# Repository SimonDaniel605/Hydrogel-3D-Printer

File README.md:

# Hydrogel-3D-Printer

This project aims at the development of a custom hydrogel 3D printer for tissue engineering and research applications for Stellenbosch University. This is a 4th year project for SU's BEng Mechatronics program.

This repository contains the PCB design files, firmware, and supporting documentation for the Hydrogel 3D Printer project.

Name: Simon Craig DANIEL

Student Number: 25848887

Supervisor: Mr. Wayne Swart

Company: Stellenbosch University

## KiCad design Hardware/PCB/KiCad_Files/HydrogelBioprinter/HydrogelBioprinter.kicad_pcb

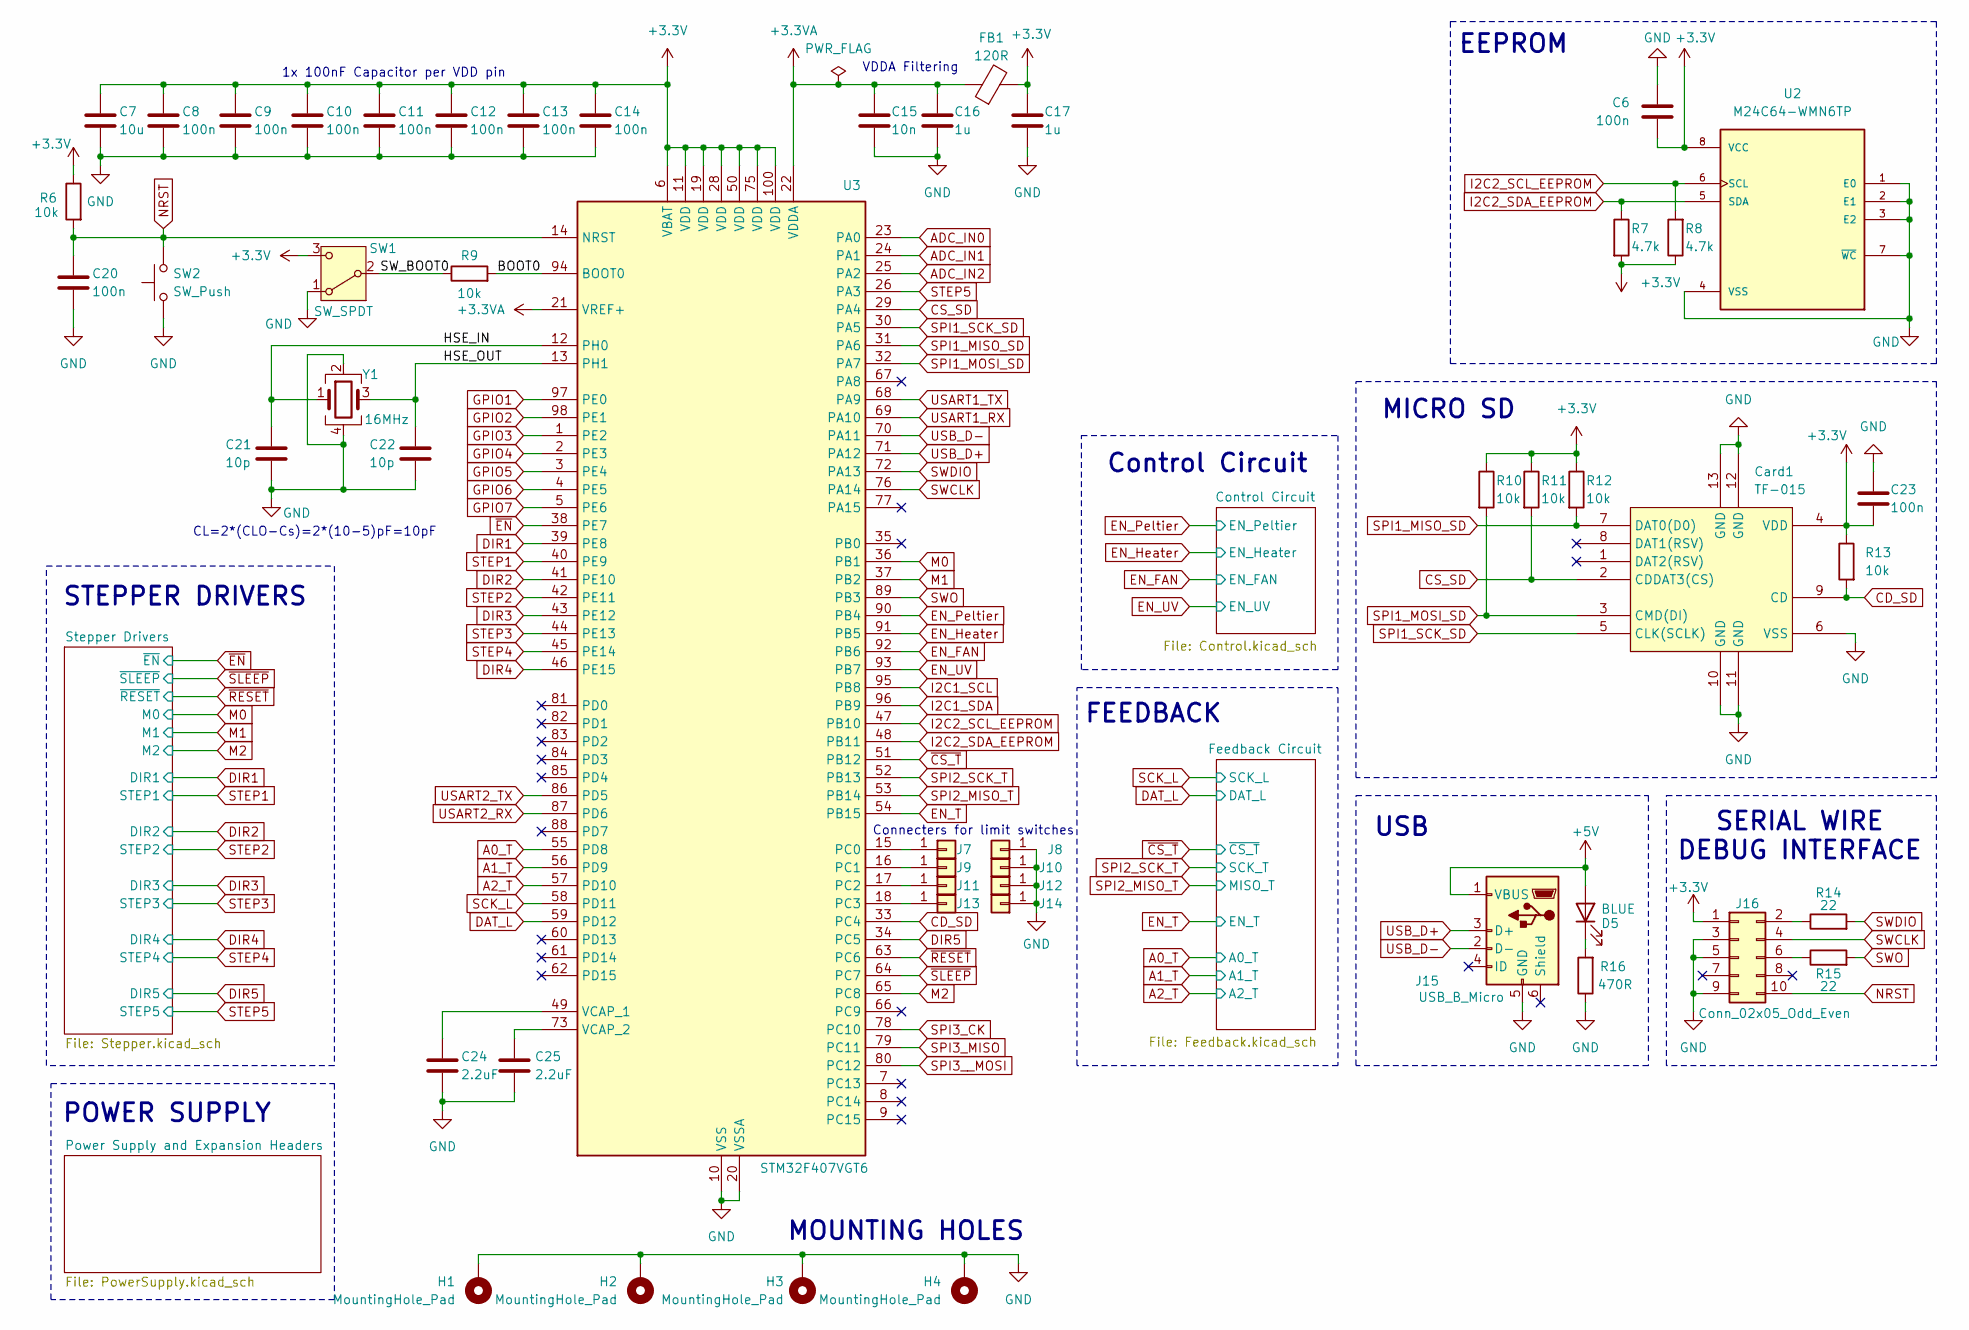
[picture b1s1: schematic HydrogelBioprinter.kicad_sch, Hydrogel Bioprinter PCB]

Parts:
C6, C8, C9, C10, C11, C12, C13, C14, C20, C23: 100n; C_0603_1608Metric
C7: 10u; C_0805_2012Metric
C15: 10n; C_0603_1608Metric
C16, C17: 1u; C_0805_2012Metric
C21, C22: 10p; C_0402_1005Metric
C24, C25: 2.2uF; C_0805_2012Metric
Card1: TF-015; TF-SMD_TF-015; LCSC Part C113206
D5: BLUE; LED_0805_2012Metric
FB1: 120R; L_0805_2012Metric
H1, H2, H3, H4: MountingHole_Pad; MountingHole_4.3mm_M4_Pad
J7, J8, J9, J10, J11, J12, J13, J14: Conn; SolderWire-0.75sqmm_1x01_D1.25mm_OD3.5mm
J15: USB_B_Micro; USB_Micro-B_Molex-105017-0001
J16: Conn_02x05_Odd_Even; PinHeader_2x05_P2.54mm_Vertical_SMD
R6, R9, R10, R11, R12, R13: 10k; R_0805_2012Metric
R7, R8: 4.7k; R_0805_2012Metric
R14, R15: 22; R_0603_1608Metric
R16: 470R; R_Axial_DIN0207_L6.3mm_D2.5mm_P10.16mm_Horizontal
SW1: SW_SPDT; SW_SPDT_PCM12
SW2: SW_Push; SW_PUSH_6mm
U2: M24C64-WMN6TP; SOIC127P600X175-8N; PARTREV 38; DigiKey_Part_Number 497-8650-2-ND
U3: STM32F407VGT6; LQFP-100_14x14mm_P0.5mm
Y1: 16MHz; Crystal_SMD_3225-4Pin_3.2x2.5mm

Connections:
+3.3V: C6.2, C7.1, C8.1, C9.1, C10.1, C11.1, C12.1, C13.1, C14.1, C17.1, C23.2, Card1.4 (VDD), FB1.2, J16.1, R6.1, R7.2, R8.1, R10.1, R11.1, R12.1, R13.1, SW1.3 (C), U2.8 (VCC), U3.6 (VBAT), U3.11 (VDD), U3.19 (VDD), U3.28 (VDD), U3.50 (VDD), U3.75 (VDD), U3.100 (VDD); also elsewhere on the board
+3.3VA: C15.1, C16.1, FB1.1, U3.21 (VREF+), U3.22 (VDDA)
+5V: D5.2 (A), J15.1 (VBUS)
/BOOT0: R9.2, U3.94 (BOOT0)
/HSE_IN: C21.1, U3.12 (PH0), Y1.1
/HSE_OUT: C22.1, U3.13 (PH1), Y1.3
/SW_BOOT0: R9.1, SW1.2 (B)
A0_T: U3.55 (PD8); also elsewhere on the board
A1_T: U3.56 (PD9); also elsewhere on the board
A2_T: U3.57 (PD10); also elsewhere on the board
ADC_IN0: U3.23 (PA0); also elsewhere on the board
ADC_IN1: U3.24 (PA1); also elsewhere on the board
ADC_IN2: U3.25 (PA2); also elsewhere on the board
CD_SD: Card1.9 (CD), R13.2, U3.33 (PC4)
CS_SD: Card1.2 (CDDAT3(CS)), R11.2, U3.29 (PA4)
DAT_L: U3.59 (PD12); also elsewhere on the board
DIR1: U3.39 (PE8); also elsewhere on the board
DIR2: U3.41 (PE10); also elsewhere on the board
DIR3: U3.43 (PE12); also elsewhere on the board
DIR4: U3.46 (PE15); also elsewhere on the board
DIR5: U3.34 (PC5); also elsewhere on the board
EN_FAN: U3.92 (PB6); also elsewhere on the board
EN_Heater: U3.91 (PB5); also elsewhere on the board
EN_Peltier: U3.90 (PB4); also elsewhere on the board
EN_T: U3.54 (PB15); also elsewhere on the board
EN_UV: U3.93 (PB7); also elsewhere on the board
GND: C6.1, C7.2, C8.2, C9.2, C10.2, C11.2, C12.2, C13.2, C14.2, C15.2, C16.2, C17.2, C20.2, C21.2, C22.2, C23.1, C24.2, C25.2, Card1.6 (VSS), Card1.10 (GND), Card1.11 (GND), Card1.12 (GND), Card1.13 (GND), H1.1, H2.1, H3.1, H4.1, J8.1, J10.1, J12.1, J14.1, J15.5 (GND), J16.3, J16.5, J16.9, R16.1, SW1.1 (A), SW2.1, U2.1 (E0), U2.2 (E1), U2.3 (E2), U2.4 (VSS), U2.7 (~WC), U3.10 (VSS), U3.20 (VSSA), U3.27 (VSS), U3.74 (VSS), U3.99 (VSS), Y1.2, Y1.4; also elsewhere on the board
GPIO1: U3.97 (PE0); also elsewhere on the board
GPIO2: U3.98 (PE1); also elsewhere on the board
GPIO3: U3.1 (PE2); also elsewhere on the board
GPIO4: U3.2 (PE3); also elsewhere on the board
GPIO5: U3.3 (PE4); also elsewhere on the board
GPIO6: U3.4 (PE5); also elsewhere on the board
GPIO7: U3.5 (PE6); also elsewhere on the board
I2C1_SCL: U3.95 (PB8); also elsewhere on the board
I2C1_SDA: U3.96 (PB9); also elsewhere on the board
I2C2_SCL_EEPROM: R8.2, U2.6 (SCL), U3.47 (PB10)
I2C2_SDA_EEPROM: R7.1, U2.5 (SDA), U3.48 (PB11)
M0: U3.36 (PB1); also elsewhere on the board
M1: U3.37 (PB2); also elsewhere on the board
M2: U3.65 (PC8); also elsewhere on the board
NRST: C20.1, J16.10, R6.2, SW2.2, U3.14 (NRST)
unnamed: D5.1 (K), R16.2
unnamed: J7.1, U3.15 (PC0)
unnamed: J9.1, U3.16 (PC1)
unnamed: J11.1, U3.17 (PC2)
unnamed: J13.1, U3.18 (PC3)
unnamed: J16.2, R14.1
unnamed: J16.6, R15.1
unnamed: C24.1, U3.49 (VCAP_1)
unnamed: C25.1, U3.73 (VCAP_2)
SCK_L: U3.58 (PD11); also elsewhere on the board
SPI1_MISO_SD: Card1.7 (DAT0(D0)), R12.2, U3.31 (PA6)
SPI1_MOSI_SD: Card1.3 (CMD(DI)), R10.2, U3.32 (PA7)
SPI1_SCK_SD: Card1.5 (CLK(SCLK)), U3.30 (PA5)
SPI2_MISO_T: U3.53 (PB14); also elsewhere on the board
SPI2_SCK_T: U3.52 (PB13); also elsewhere on the board
SPI3_CK: U3.78 (PC10); also elsewhere on the board
SPI3_MISO: U3.79 (PC11); also elsewhere on the board
SPI3__MOSI: U3.80 (PC12); also elsewhere on the board
STEP1: U3.40 (PE9); also elsewhere on the board
STEP2: U3.42 (PE11); also elsewhere on the board
STEP3: U3.44 (PE13); also elsewhere on the board
STEP4: U3.45 (PE14); also elsewhere on the board
STEP5: U3.26 (PA3); also elsewhere on the board
SWCLK: J16.4, U3.76 (PA14)
SWDIO: R14.2, U3.72 (PA13)
SWO: R15.2, U3.89 (PB3)
USART1_RX: U3.69 (PA10); also elsewhere on the board
USART1_TX: U3.68 (PA9); also elsewhere on the board
USART2_RX: U3.87 (PD6); also elsewhere on the board
USART2_TX: U3.86 (PD5); also elsewhere on the board
USB_D+: J15.3 (D+), U3.71 (PA12)
USB_D-: J15.2 (D-), U3.70 (PA11)
~CS_T: U3.51 (PB12); also elsewhere on the board
~EN: U3.38 (PE7); also elsewhere on the board
~RESET: U3.63 (PC6); also elsewhere on the board
~SLEEP: U3.64 (PC7); also elsewhere on the board

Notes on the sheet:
VDDA Filtering
FEEDBACK
SERIAL WIRE DEBUG INTERFACE
Connecters for limit switches
USB
MOUNTING HOLES
MICRO SD
STEPPER DRIVERS
CL=2*(CLO-Cs)=2*(10-5)pF=10pF
Control Circuit
EEPROM
POWER SUPPLY
1x 100nF Capacitor per VDD pin

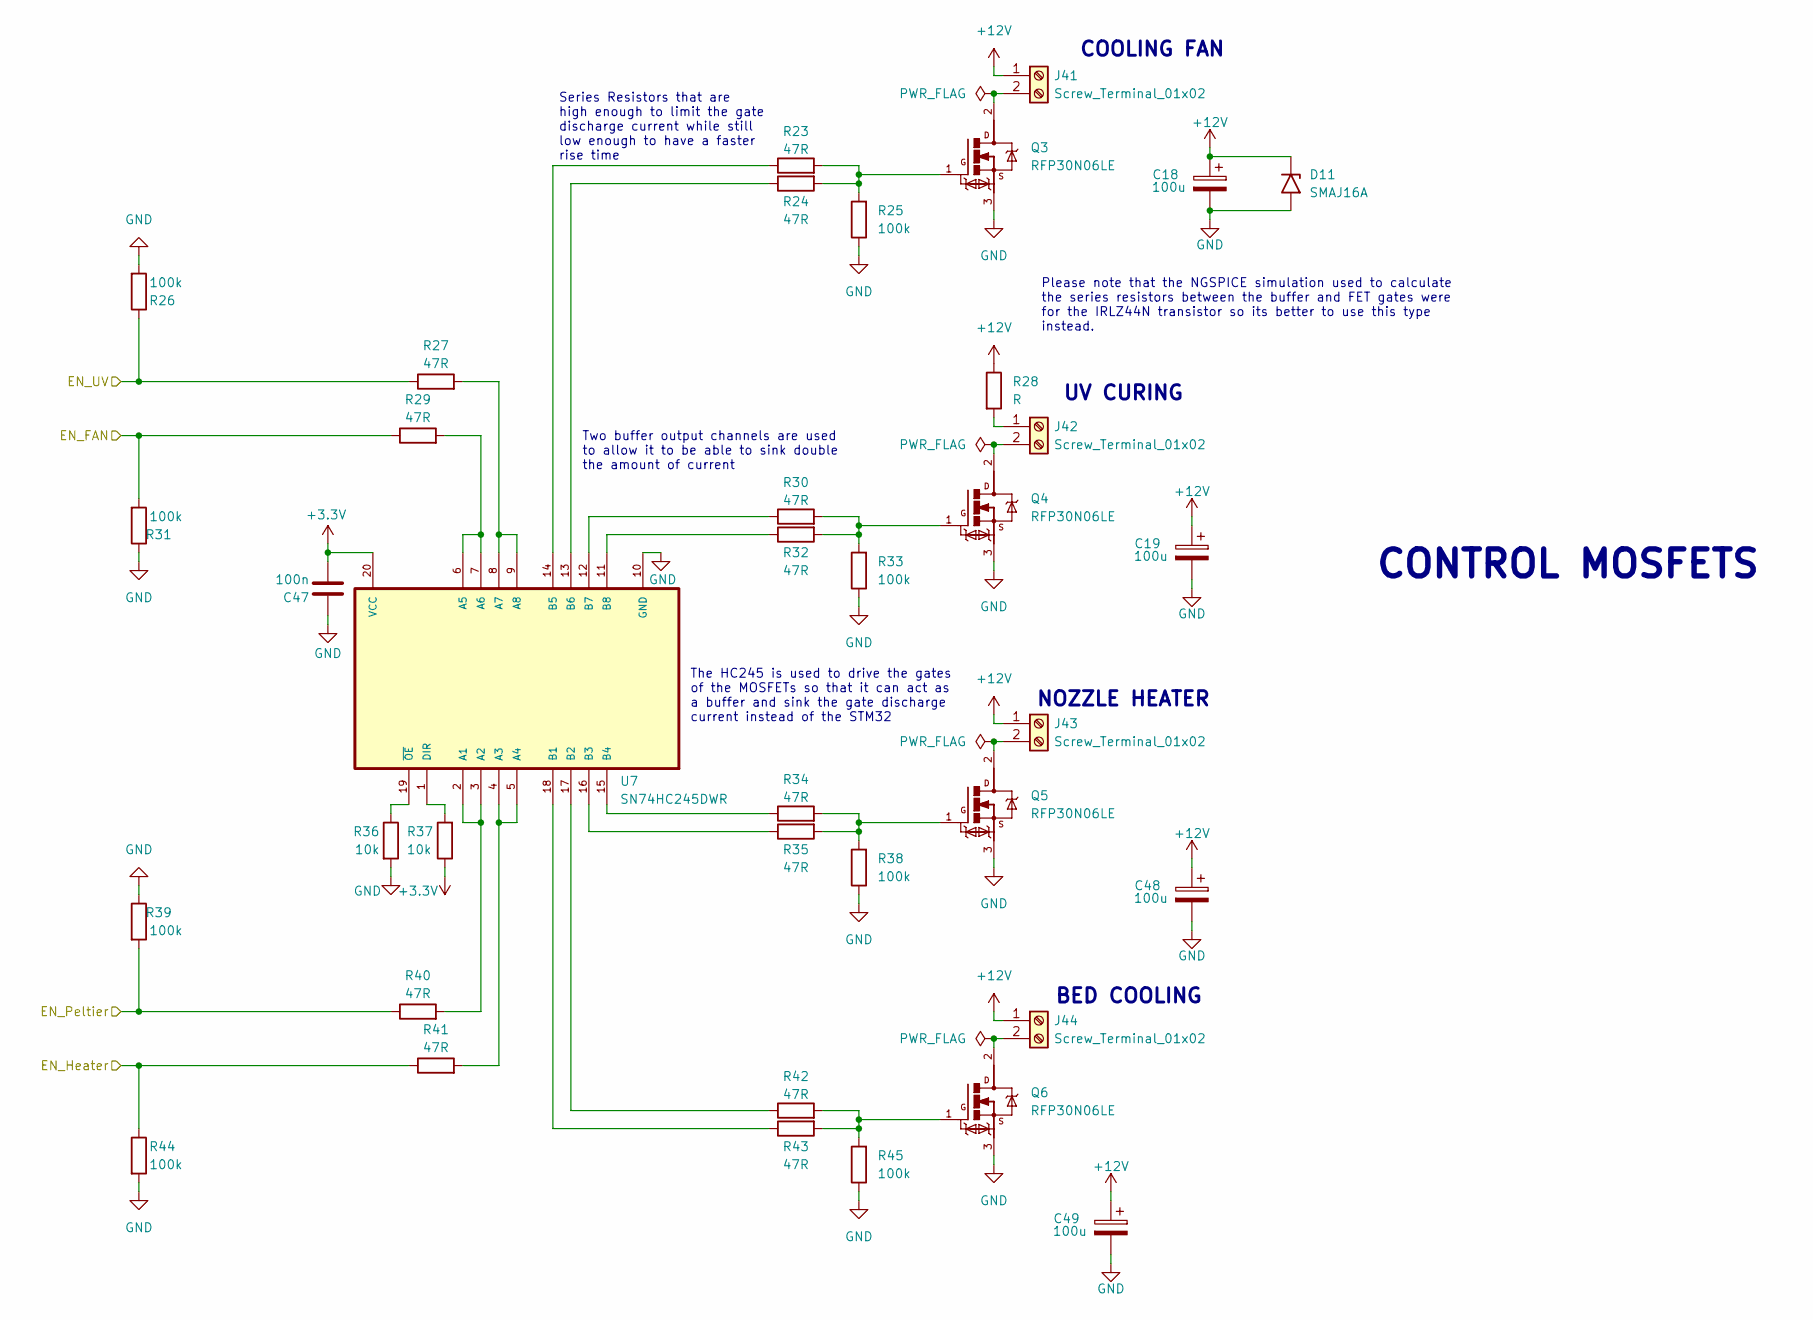
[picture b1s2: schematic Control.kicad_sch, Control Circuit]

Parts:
C18, C19, C48, C49: 100u; CP_Elec_6.3x7.7
C47: 100n; C_0603_1608Metric
D11: SMAJ16A; D_SMA
J41, J42, J43, J44: Screw_Terminal_01x02; TerminalBlock_Phoenix_MKDS-1,5-2-5.08_1x02_P5.08mm_Horizont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
Q3, Q4, Q5, Q6: RFP30N06LE; TRANS_RFP30N06LE
R23, R24, R27, R29, R30, R32, R34, R35, R40, R41, R42, R43: 47R; R_0805_2012Metric
R25, R26, R31, R33, R38, R39, R44, R45: 100k; R_0805_2012Metric
R28: R; R_Axial_DIN0207_L6.3mm_D2.5mm_P10.16mm_Horizontal
R36, R37: 10k; R_0805_2012Metric
U7: SN74HC245DWR; SOIC127P1030X265-20N

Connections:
+3.3V: C47.1, R37.1, U7.20 (VCC); also elsewhere on the board
+12V: C18.1, C19.1, C48.1, C49.1, D11.1 (A1), J41.1, J43.1, J44.1, R28.1; also elsewhere on the board
EN_FAN: R29.1, R31.2; also elsewhere on the board
EN_Heater: R41.1, R44.1; also elsewhere on the board
EN_Peltier: R39.2, R40.1; also elsewhere on the board
EN_UV: R26.1, R27.1; also elsewhere on the board
GND: C18.2, C19.2, C47.2, C48.2, C49.2, D11.2 (A2), Q3.3, Q4.3, Q5.3, Q6.3, R25.1, R26.2, R31.1, R33.1, R36.2, R38.1, R39.1, R44.2, R45.1, U7.10 (GND); also elsewhere on the board
unnamed: J41.2, Q3.2
unnamed: J42.1, R28.2
unnamed: J42.2, Q4.2
unnamed: J43.2, Q5.2
unnamed: J44.2, Q6.2
unnamed: Q3.1, R23.2, R24.2, R25.2
unnamed: Q4.1, R30.2, R32.2, R33.2
unnamed: Q5.1, R34.2, R35.2, R38.2
unnamed: Q6.1, R42.2, R43.2, R45.2
unnamed: R40.2, U7.2 (A1), U7.3 (A2)
unnamed: R41.2, U7.4 (A3), U7.5 (A4)
unnamed: R29.2, U7.6 (A5), U7.7 (A6)
unnamed: R27.2, U7.8 (A7), U7.9 (A8)
unnamed: R43.1, U7.18 (B1)
unnamed: R42.1, U7.17 (B2)
unnamed: R35.1, U7.16 (B3)
unnamed: R34.1, U7.15 (B4)
unnamed: R23.1, U7.14 (B5)
unnamed: R24.1, U7.13 (B6)
unnamed: R30.1, U7.12 (B7)
unnamed: R32.1, U7.11 (B8)
unnamed: R37.2, U7.1 (DIR)
unnamed: R36.1, U7.19 (~OE)

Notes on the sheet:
UV CURING
NOZZLE HEATER
COOLING FAN
Two buffer output channels are used to allow it to be able to sink double the amount of current
The HC245 is used to drive the gates of the MOSFETs so that it can act as a buffer and sink the gate discharge current instead of the STM32
Please note that the NGSPICE simulation used to calculate the series resistors between the buffer and FET gates were for the IRLZ44N transistor so its better to use this type instead.
CONTROL MOSFETS
Series Resistors that are high enough to limit the gate discharge current while still low enough to have a faster rise time
BED COOLING

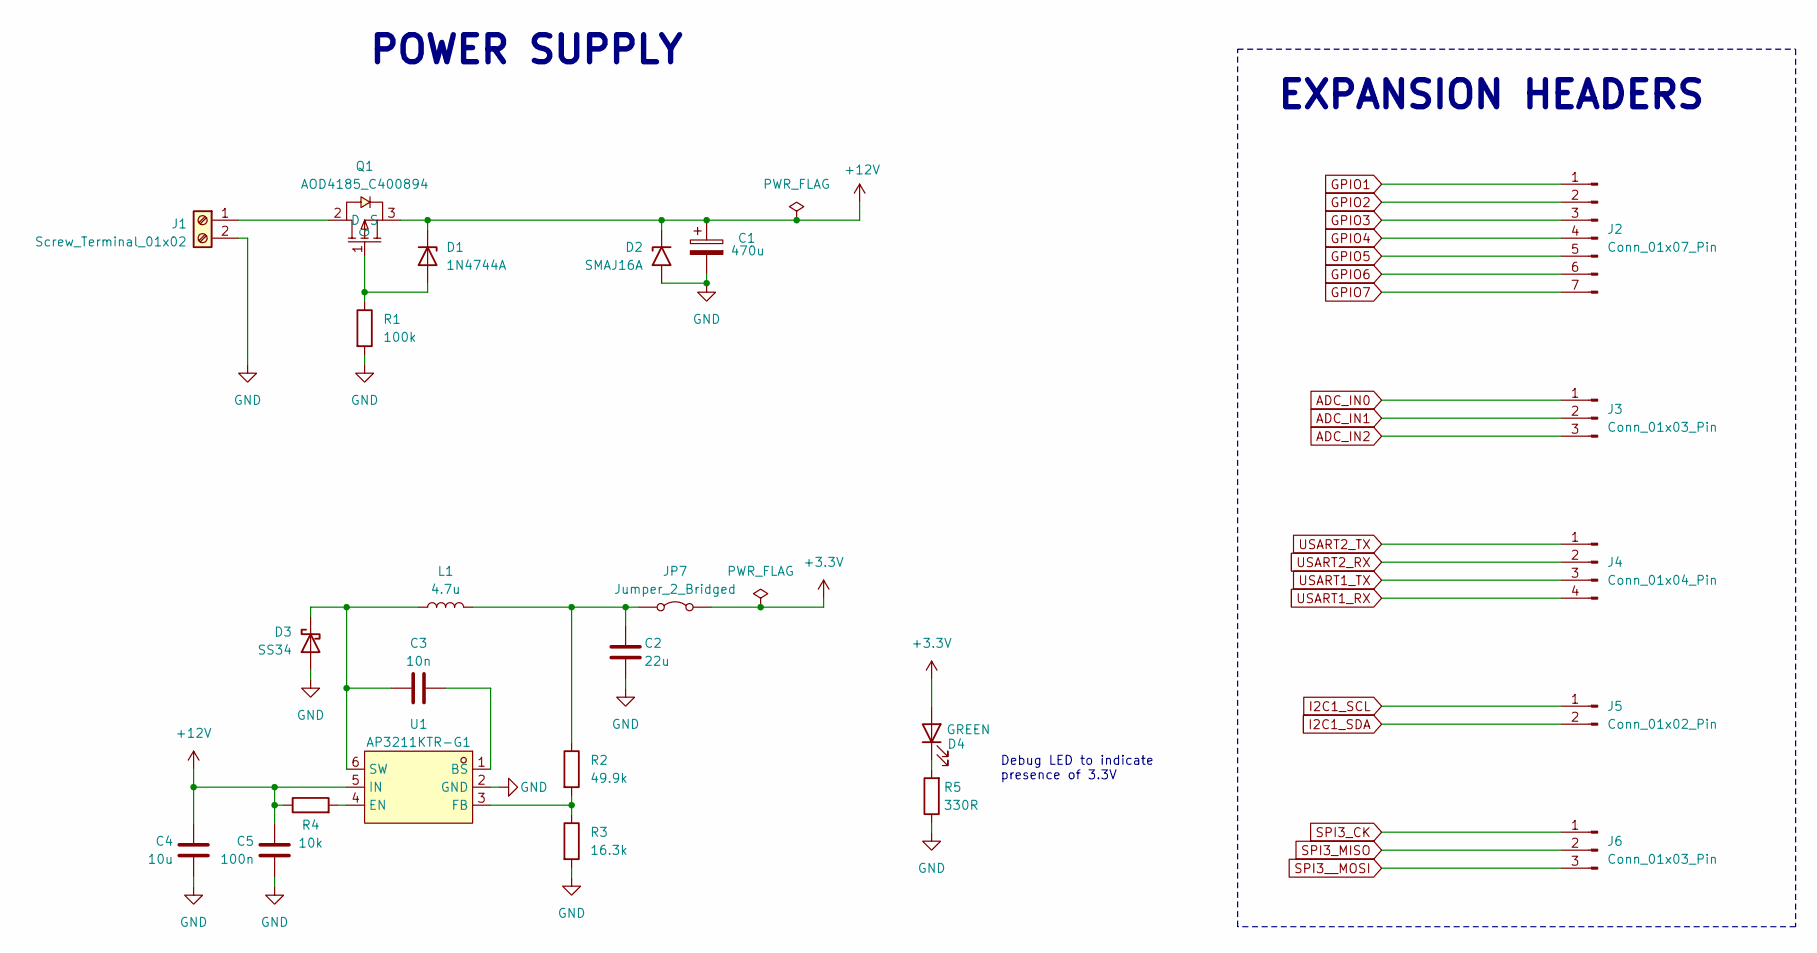
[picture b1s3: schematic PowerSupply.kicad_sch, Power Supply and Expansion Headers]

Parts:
C1: 470u; CP_Radial_D10.0mm_P5.00mm
C2: 22u; C_0805_2012Metric
C3: 10n; C_0603_1608Metric
C4: 10u; C_0805_2012Metric
C5: 100n; C_0603_1608Metric
D1: 1N4744A; D_DO-41_SOD81_P10.16mm_Horizontal
D2: SMAJ16A; D_SMA
D3: SS34; D_SMA
D4: GREEN; LED_0805_2012Metric
J1: Screw_Terminal_01x02; TerminalBlock_Phoenix_MKDS-1,5-2-5.08_1x02_P5.08mm_Horizont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
J2: Conn_01x07_Pin; PinHeader_1x07_P2.54mm_Vertical
J3, J6: Conn_01x03_Pin; PinHeader_1x03_P2.54mm_Vertical
J4: Conn_01x04_Pin; PinHeader_1x04_P2.54mm_Vertical
J5: Conn_01x02_Pin; PinHeader_1x02_P2.54mm_Vertical
JP7: Jumper_2_Bridged; TestPoint_2Pads_Pitch2.54mm_Drill0.8mm
L1: 4.7u; L_7.3x7.3_H4.5
Q1: AOD4185_C400894; TO-252-3_L6.6-W6.1-P4.57-LS9.9-BR-CW; LCSC Part C400894
R1: 100k; R_0805_2012Metric
R2: 49.9k; R_Axial_DIN0207_L6.3mm_D2.5mm_P10.16mm_Horizontal
R3: 16.3k; R_Axial_DIN0207_L6.3mm_D2.5mm_P10.16mm_Horizontal
R4: 10k; R_0805_2012Metric
R5: 330R; R_Axial_DIN0207_L6.3mm_D2.5mm_P10.16mm_Horizontal
U1: AP3211KTR-G1; LCSC Part C154863

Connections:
+3.3V: D4.2 (A), JP7.1 (A); also elsewhere on the board
+12V: C1.1, C4.2, C5.2, D1.1 (K), D2.1 (A1), Q1.3 (S), R4.1, U1.5 (IN); also elsewhere on the board
ADC_IN0: J3.1; also elsewhere on the board
ADC_IN1: J3.2; also elsewhere on the board
ADC_IN2: J3.3; also elsewhere on the board
GND: C1.2, C2.2, C4.1, C5.1, D2.2 (A2), D3.2 (A), J1.2, R1.2, R3.2, R5.1, U1.2 (GND); also elsewhere on the board
GPIO1: J2.1; also elsewhere on the board
GPIO2: J2.2; also elsewhere on the board
GPIO3: J2.3; also elsewhere on the board
GPIO4: J2.4; also elsewhere on the board
GPIO5: J2.5; also elsewhere on the board
GPIO6: J2.6; also elsewhere on the board
GPIO7: J2.7; also elsewhere on the board
I2C1_SCL: J5.1; also elsewhere on the board
I2C1_SDA: J5.2; also elsewhere on the board
unnamed: D1.2 (A), Q1.1 (G), R1.1
unnamed: C3.1, D3.1 (K), L1.1, U1.6 (SW)
unnamed: D4.1 (K), R5.2
unnamed: J1.1, Q1.2 (D)
unnamed: C2.1, JP7.2 (B), L1.2, R2.1
unnamed: C3.2, U1.1 (BS)
unnamed: R4.2, U1.4 (EN)
unnamed: R2.2, R3.1, U1.3 (FB)
SPI3_CK: J6.1; also elsewhere on the board
SPI3_MISO: J6.2; also elsewhere on the board
SPI3__MOSI: J6.3; also elsewhere on the board
USART1_RX: J4.4; also elsewhere on the board
USART1_TX: J4.3; also elsewhere on the board
USART2_RX: J4.2; also elsewhere on the board
USART2_TX: J4.1; also elsewhere on the board

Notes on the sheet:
EXPANSION HEADERS
POWER SUPPLY
Debug LED to indicate presence of 3.3V

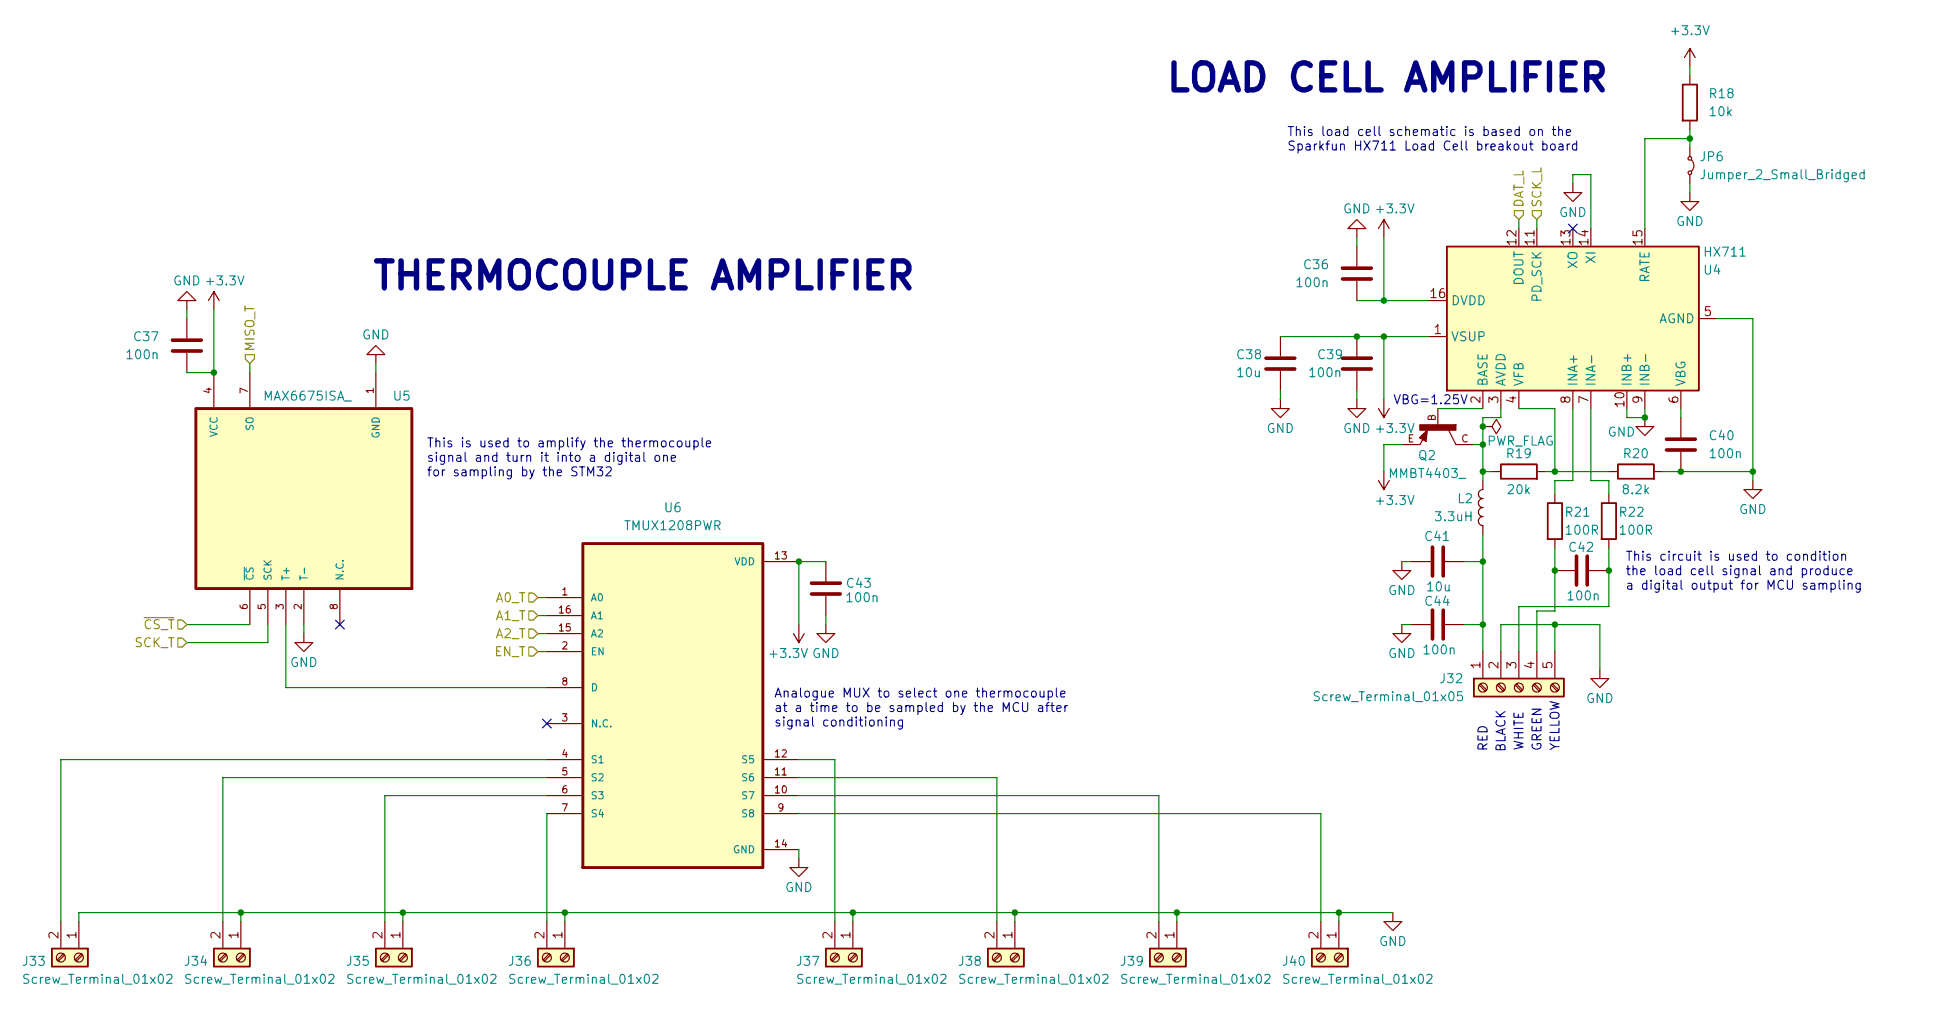
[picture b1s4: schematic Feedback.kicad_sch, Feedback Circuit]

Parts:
C36, C37, C39, C40, C42, C43, C44: 100n; C_0603_1608Metric
C38, C41: 10u; C_0805_2012Metric
J32: Screw_Terminal_01x05; TerminalBlock_Phoenix_PT-1,5-5-3.5-H_1x05_P3.50mm_Horizontal
J33, J34, J35, J36, J37, J38, J39, J40: Screw_Terminal_01x02; TerminalBlock_Phoenix_PT-1,5-2-3.5-H_1x02_P3.50mm_Horizontal
JP6: Jumper_2_Small_Bridged; TestPoint_2Pads_Pitch2.54mm_Drill0.8mm
L2: 3.3uH; L_0805_2012Metric
Q2: MMBT4403_; SOT23-BEC
R18: 10k; R_0805_2012Metric
R19: 20k; R_0805_2012Metric
R20: 8.2k; R_0805_2012Metric
R21, R22: 100R; R_0603_1608Metric
U4: HX711; SOP-16_3.9x9.9mm_P1.27mm
U5: MAX6675ISA_; SOIC127P600X175-8N
U6: TMUX1208PWR; SOP65P640X120-16N

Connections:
+3.3V: C36.2, C37.2, C38.2, C39.2, C43.2, Q2.E, R18.1, U4.1 (VSUP), U4.16 (DVDD), U5.4 (VCC), U6.13 (VDD); also elsewhere on the board
A0_T: U6.1 (A0); also elsewhere on the board
A1_T: U6.16 (A1); also elsewhere on the board
A2_T: U6.15 (A2); also elsewhere on the board
DAT_L: U4.12 (DOUT); also elsewhere on the board
EN_T: U6.2 (EN); also elsewhere on the board
GND: C36.1, C37.1, C38.1, C39.1, C40.2, C41.2, C43.1, C44.2, J32.2, J32.5, J33.1, J34.1, J35.1, J36.1, J37.1, J38.1, J39.1, J40.1, JP6.2 (B), R20.2, U4.5 (AGND), U4.9 (INB-), U4.10 (INB+), U4.14 (XI), U5.1 (GND), U5.2 (T-), U6.14 (GND); also elsewhere on the board
unnamed: C41.1, C44.1, J32.1, L2.2
unnamed: C42.1, J32.3, R22.2
unnamed: C42.2, J32.4, R21.2
unnamed: J33.2, U6.4 (S1)
unnamed: J34.2, U6.5 (S2)
unnamed: J35.2, U6.6 (S3)
unnamed: J36.2, U6.7 (S4)
unnamed: J37.2, U6.12 (S5)
unnamed: J38.2, U6.11 (S6)
unnamed: J39.2, U6.10 (S7)
unnamed: J40.2, U6.9 (S8)
unnamed: JP6.1 (A), R18.2, U4.15 (RATE)
unnamed: L2.1, Q2.C, R19.1, U4.3 (AVDD)
unnamed: Q2.B, U4.2 (BASE)
unnamed: R21.1, U4.8 (INA+)
unnamed: R22.1, U4.7 (INA-)
unnamed: C40.1, U4.6 (VBG)
unnamed: R19.2, R20.1, U4.4 (VFB)
unnamed: U5.3 (T+), U6.8 (D)
SCK_L: U4.11 (PD_SCK); also elsewhere on the board
SPI2_MISO_T: U5.7 (SO); also elsewhere on the board
SPI2_SCK_T: U5.5 (SCK); also elsewhere on the board
~CS_T: U5.6 (~CS); also elsewhere on the board

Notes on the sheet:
WHITE
This load cell schematic is based on the Sparkfun HX711 Load Cell breakout board
THERMOCOUPLE AMPLIFIER
YELLOW
This circuit is used to condition the load cell signal and produce a digital output for MCU sampling
BLACK
RED
GREEN
Analogue MUX to select one thermocouple at a time to be sampled by the MCU after signal conditioning
LOAD CELL AMPLIFIER
VBG=1.25V
This is used to amplify the thermocouple signal and turn it into a digital one for sampling by the STM32

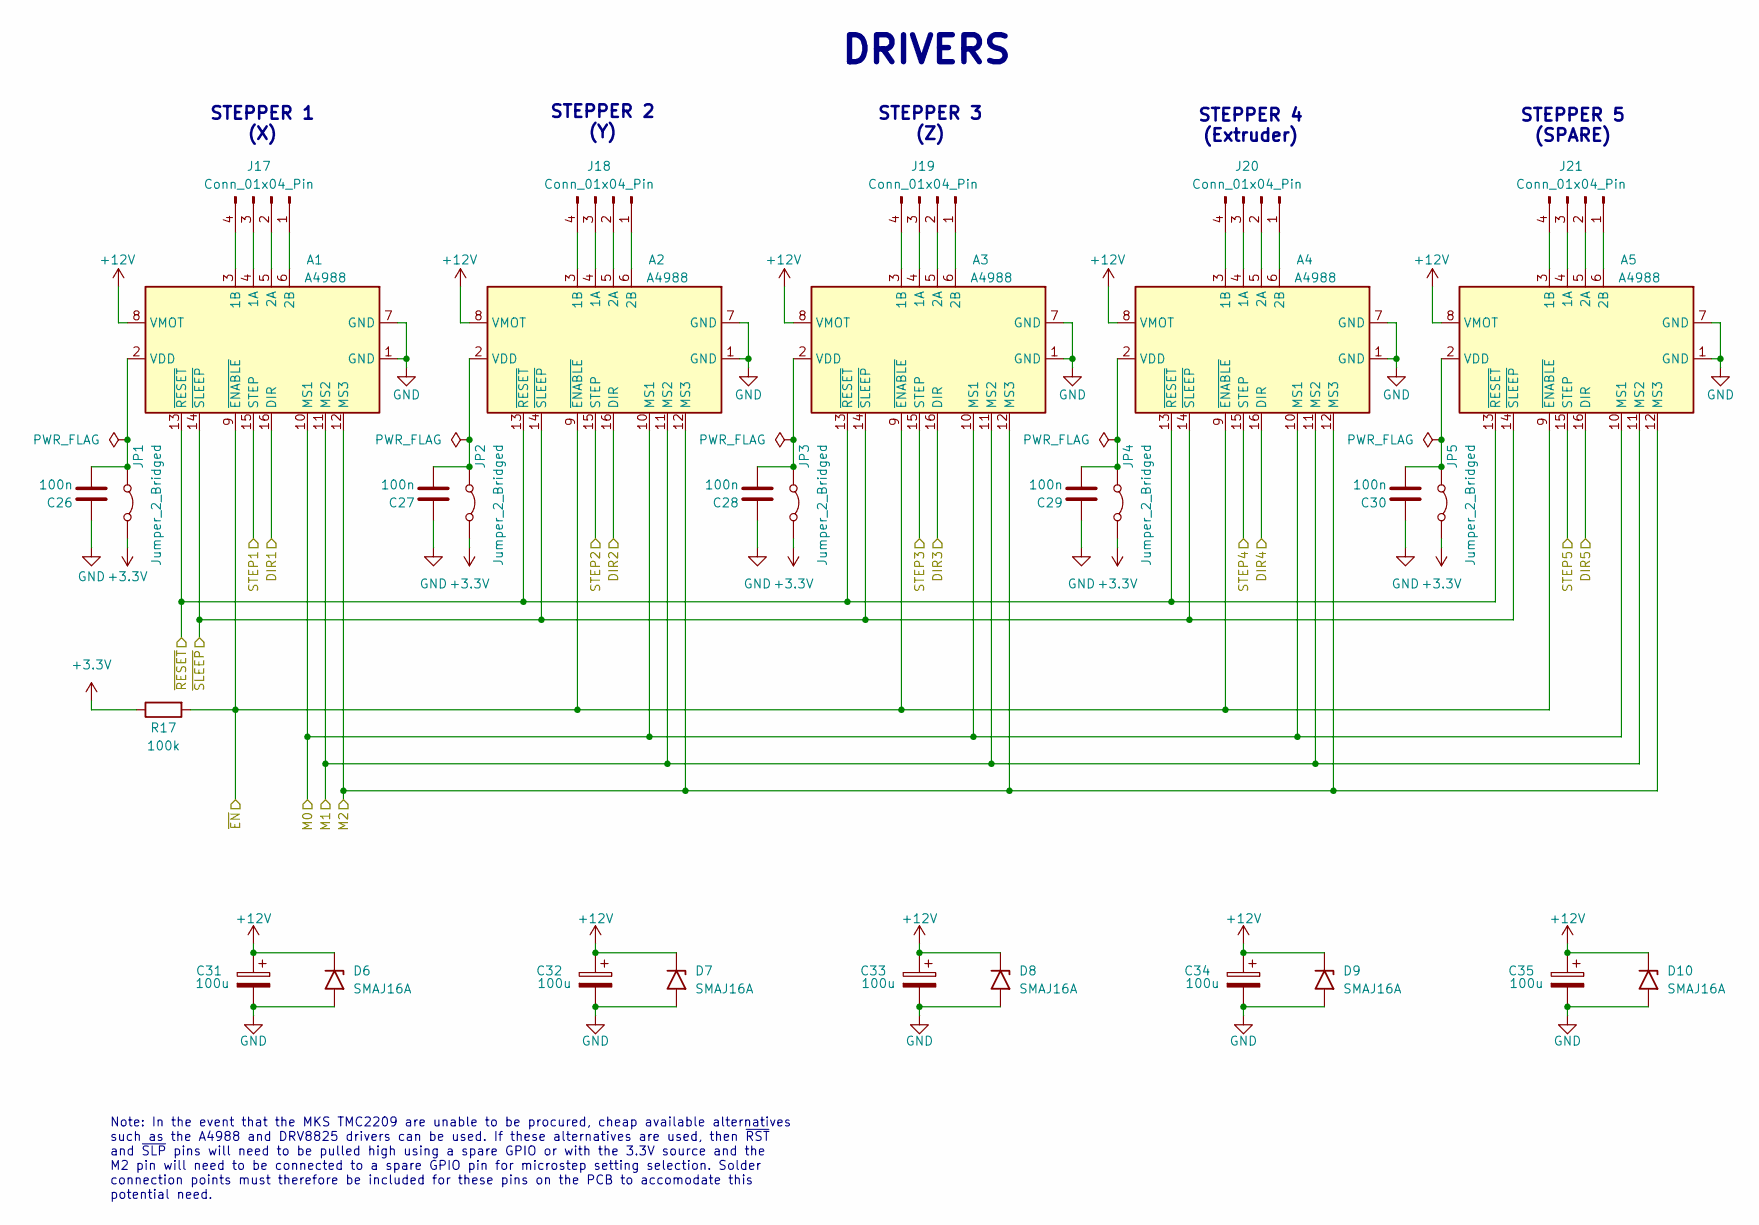
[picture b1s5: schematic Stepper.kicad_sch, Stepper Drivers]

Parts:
A1, A2, A3, A4, A5: A4988; Pololu_Breakout-16_15.2x20.3mm
C26, C27, C28, C29, C30: 100n; C_0603_1608Metric
C31, C32, C33, C34, C35: 100u; CP_Elec_6.3x7.7
D6, D7, D8, D9, D10: SMAJ16A; D_SMA
J17, J18, J19, J20, J21: Conn_01x04_Pin; PinHeader_1x04_P2.54mm_Vertical
JP1, JP2, JP3, JP4, JP5: Jumper_2_Bridged; TestPoint_2Pads_Pitch2.54mm_Drill0.8mm
R17: 100k; R_0805_2012Metric

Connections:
+3.3V: JP1.2 (B), JP2.2 (B), JP3.2 (B), JP4.2 (B), JP5.2 (B), R17.1; also elsewhere on the board
+12V: A1.8 (VMOT), A2.8 (VMOT), A3.8 (VMOT), A4.8 (VMOT), A5.8 (VMOT), C31.1, C32.1, C33.1, C34.1, C35.1, D6.1 (A1), D7.1 (A1), D8.1 (A1), D9.1 (A1), D10.1 (A1); also elsewhere on the board
DIR1: A1.16 (DIR); also elsewhere on the board
DIR2: A2.16 (DIR); also elsewhere on the board
DIR3: A3.16 (DIR); also elsewhere on the board
DIR4: A4.16 (DIR); also elsewhere on the board
DIR5: A5.16 (DIR); also elsewhere on the board
GND: A1.1 (GND), A1.7 (GND), A2.1 (GND), A2.7 (GND), A3.1 (GND), A3.7 (GND), A4.1 (GND), A4.7 (GND), A5.1 (GND), A5.7 (GND), C26.1, C27.1, C28.1, C29.1, C30.1, C31.2, C32.2, C33.2, C34.2, C35.2, D6.2 (A2), D7.2 (A2), D8.2 (A2), D9.2 (A2), D10.2 (A2); also elsewhere on the board
M0: A1.10 (MS1), A2.10 (MS1), A3.10 (MS1), A4.10 (MS1), A5.10 (MS1); also elsewhere on the board
M1: A1.11 (MS2), A2.11 (MS2), A3.11 (MS2), A4.11 (MS2), A5.11 (MS2); also elsewhere on the board
M2: A1.12 (MS3), A2.12 (MS3), A3.12 (MS3), A4.12 (MS3), A5.12 (MS3); also elsewhere on the board
unnamed: A1.4 (1A), J17.3
unnamed: A1.3 (1B), J17.4
unnamed: A1.5 (2A), J17.2
unnamed: A1.6 (2B), J17.1
unnamed: A1.2 (VDD), C26.2, JP1.1 (A)
unnamed: A2.4 (1A), J18.3
unnamed: A2.3 (1B), J18.4
unnamed: A2.5 (2A), J18.2
unnamed: A2.6 (2B), J18.1
unnamed: A2.2 (VDD), C27.2, JP2.1 (A)
unnamed: A3.4 (1A), J19.3
unnamed: A3.3 (1B), J19.4
unnamed: A3.5 (2A), J19.2
unnamed: A3.6 (2B), J19.1
unnamed: A3.2 (VDD), C28.2, JP3.1 (A)
unnamed: A4.4 (1A), J20.3
unnamed: A4.3 (1B), J20.4
unnamed: A4.5 (2A), J20.2
unnamed: A4.6 (2B), J20.1
unnamed: A4.2 (VDD), C29.2, JP4.1 (A)
unnamed: A5.4 (1A), J21.3
unnamed: A5.3 (1B), J21.4
unnamed: A5.5 (2A), J21.2
unnamed: A5.6 (2B), J21.1
unnamed: A5.2 (VDD), C30.2, JP5.1 (A)
STEP1: A1.15 (STEP); also elsewhere on the board
STEP2: A2.15 (STEP); also elsewhere on the board
STEP3: A3.15 (STEP); also elsewhere on the board
STEP4: A4.15 (STEP); also elsewhere on the board
STEP5: A5.15 (STEP); also elsewhere on the board
~EN: A1.9 (~ENABLE), A2.9 (~ENABLE), A3.9 (~ENABLE), A4.9 (~ENABLE), A5.9 (~ENABLE), R17.2; also elsewhere on the board
~RESET: A1.13 (~RESET), A2.13 (~RESET), A3.13 (~RESET), A4.13 (~RESET), A5.13 (~RESET); also elsewhere on the board
~SLEEP: A1.14 (~SLEEP), A2.14 (~SLEEP), A3.14 (~SLEEP), A4.14 (~SLEEP), A5.14 (~SLEEP); also elsewhere on the board

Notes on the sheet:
STEPPER 1 (X)
STEPPER 3 (Z)
STEPPER 2 (Y)
DRIVERS
STEPPER 5 (SPARE)
STEPPER 4 (Extruder)
Note: In the event that the MKS TMC2209 are unable to be procured, cheap available alternatives such as the A4988 and DRV8825 drivers can be used. If these alternatives are used, then ~{RST} and ~{SLP} pins will need to be pulled high using a spare GPIO or with the 3.3V source and the M2 pin will n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
